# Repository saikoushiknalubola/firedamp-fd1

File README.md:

# Firedamp Dynamics · FD-1 Borehole Sentinel

**Vishwakarma Awards 2026-27** · Sustainable Mining (IIT Hyderabad) · Application ID **VK26-IITH-SM-0008**

**Team Chakra**
- Saikoushik Nalubola (lead), B.Tech CSE (AI & ML), SR University, Warangal
- Devara Aravind, Mining Engineering, University College of Engineering, Osmania University
- Atthe Durga Raj, Mining Engineering, JNTUH University College of Engineering Manthani

India drains methane out of its gassiest coal seams for safety, then mostly lets it go. Ember (2026) found no commercial coal mine methane project running in the country, while emissions are on track to pass 1.6 Mt a year by the end of the decade. Gas can only be used or flared safely when its quality is known, and a single leaking borehole collar can dilute a whole drainage range toward the 5-15% explosive band without anyone seeing which hole is at fault.

Firedamp Dynamics is a five-stage capture system: drainage, conditioning, utilisation, destruction and MRV. **FD-1 is the module we build first.** It sits on each borehole and does four things:

- measures methane (NDIR), oxygen, flow (ISO 5167 orifice) and line pressure at that hole, once a second
- throttles the hole when air leaks in, and isolates it below 25% CH4 or above 10% O2
- checks itself: methane from the NDIR must agree with methane implied by oxygen (1 − O2/20.95)
- logs per-borehole methane totals for MRV, corrected for gas density

## Key numbers

| | |
|---|---|
| Routing bands | route ≥ 30% CH4 (2 × upper explosive limit, UNECE 2016) · throttle 25-30% · isolate < 25% |
| Leak model | moderate leak held at ≥ 28.5% CH4 by throttling; gross leak isolated at 331 s; unmanaged range falls to 17.0% |
| Flow accuracy | density correction removes a 14.4% under-read at 60% CH4 |
| Bracket FEA | rev A FoS 1.87 → rev B FoS 3.87 (12 kg spool at 4 g, Al 6061-T6) |
| Electronics | KiCad 7 schematic (44 parts, 44 nets) and routed 2-layer PCB, 110 × 80 mm, DRC 0 errors |
| Cost | ₹35,400 per complete node · ₹48,400 for the full Stage 3 build incl. bench rig (approximate quotes, Oct 2026) |
| Value | one borehole draining 0.3 m3/min CH4 ≈ $190/day of gas at Ember's import-offset rate |

Every number has a source or a script: see [docs/sources.md](docs/sources.md).

## Repository

| Path | Contents |
|---|---|
| `cad/src/fd1_assembly.py` | Parametric CadQuery model, 24 parts, driven by one parameter block |
| `cad/step/`, `cad/stl/` | STEP for every part plus the assembly; STL for printing (chamber, servo bracket) |
| `electronics/kicad/` | Native KiCad 7 schematic + PCB, netlist, DRC report, Specctra files, generators, renderer |
| `electronics/bom.csv` | Itemised BOM with price basis for every line and the cost decisions behind it |
| `firmware/fd1_node/` | ESP32-S3 firmware: state machine, flow maths, MRV totals, pin map, thresholds |
| `analysis/` | Bracket FEA (scikit-fem), gas and orifice calculations, closed-loop leak model, unit economics |
| `docs/` | Diagram scripts, all deck figures, sources, patent notes |
| `test-rig/test_plan.md` | Eight bench tests with pass criteria |

## Reproduce

```bash
pip install cadquery trimesh scikit-fem matplotlib numpy scipy pygments
python cad/src/fd1_assembly.py && python cad/src/render.py
python analysis/bracket_fea.py && python analysis/gas_calcs.py && python analysis/leak_sim.py
python electronics/bom.py && python electronics/schematic.py
python docs/diagrams.py && python docs/research_figures.py
# KiCad 7 + Freerouting 1.9
cd electronics/kicad && python gen_schematic.py \
  && kicad-cli sch export netlist fd1_controller.kicad_sch -o fd1_controller.net \
  && python check_netlist.py \
  && python gen_pcb.py place \
  && java -jar freerouting-1.9.0.jar -de fd1_controller.dsn -do fd1_controller.ses -mp 60 \
  && python gen_pcb.py finish && python render_pcb.py
```

## Safety

The bench rig runs on CO2 as a non-flammable stand-in for seam gas, with purity read from the O2 cell. The only methane on the bench is a small certified span cylinder at 2.5% (below the lower explosive limit). The prototype is not Ex certified and will not go underground; field equipment needs DGMS approval under the Coal Mines Regulations 2017 and an IEC 60079 Group I design.

## Status

Stage 2 design complete, including a DRC-checked PCB. Next: Gerbers to fab, sensor drivers replacing the firmware stubs, rig build and calibration (roadmap in the deck).

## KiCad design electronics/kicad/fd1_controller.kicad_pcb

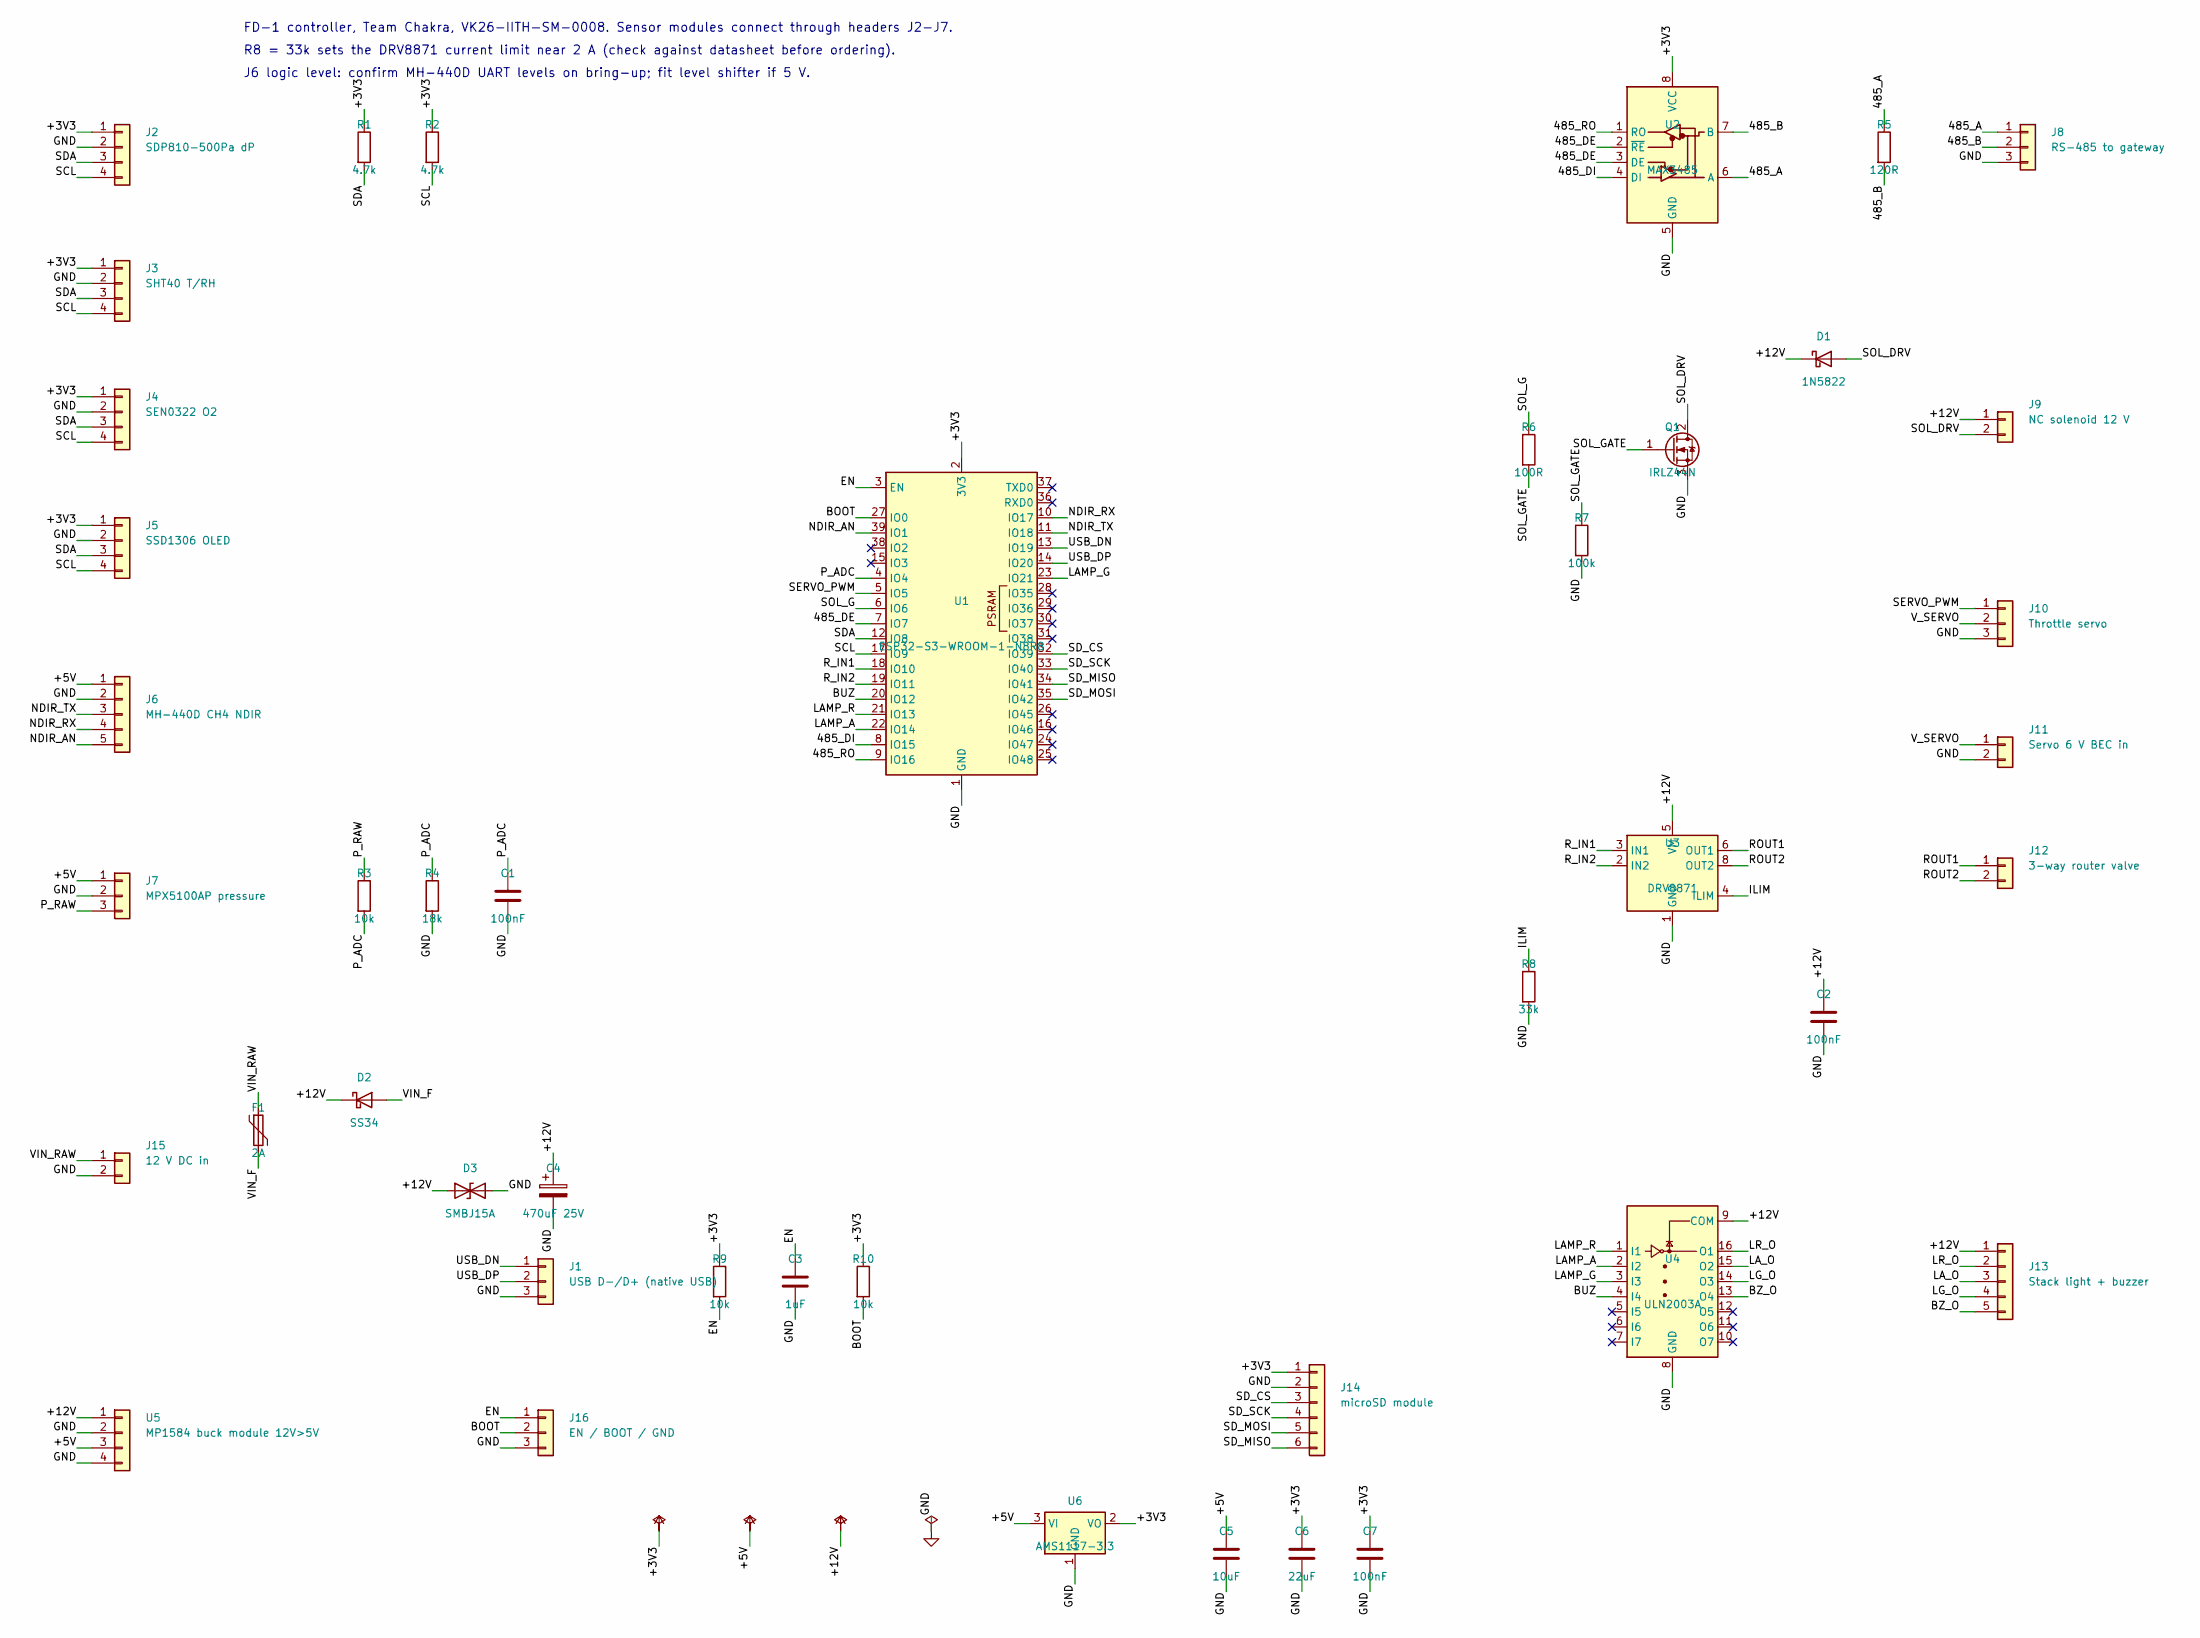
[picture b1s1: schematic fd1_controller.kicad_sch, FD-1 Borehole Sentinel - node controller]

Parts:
C1, C2, C7: 100nF; C_0805_2012Metric
C3: 1uF; C_0805_2012Metric
C4: 470uF 25V; CP_Radial_D10.0mm_P5.00mm
C5: 10uF; C_0805_2012Metric
C6: 22uF; C_0805_2012Metric
D1: 1N5822; D_DO-201AD_P15.24mm_Horizontal
D2: SS34; D_SMA
D3: SMBJ15A; D_SMB
F1: 2A; Fuse_1812_4532Metric
J1: USB D-/D+ (native USB); PinHeader_1x03_P2.54mm_Vertical
J2: SDP810-500Pa dP; PinHeader_1x04_P2.54mm_Vertical
J3: SHT40 T/RH; PinHeader_1x04_P2.54mm_Vertical
J4: SEN0322 O2; PinHeader_1x04_P2.54mm_Vertical
J5: SSD1306 OLED; PinHeader_1x04_P2.54mm_Vertical
J6: MH-440D CH4 NDIR; PinHeader_1x05_P2.54mm_Vertical
J7: MPX5100AP pressure; PinHeader_1x03_P2.54mm_Vertical
J8: RS-485 to gateway; TerminalBlock_bornier-3_P5.08mm
J9: NC solenoid 12 V; TerminalBlock_bornier-2_P5.08mm
J10: Throttle servo; PinHeader_1x03_P2.54mm_Vertical
J11: Servo 6 V BEC in; PinHeader_1x02_P2.54mm_Vertical
J12: 3-way router valve; TerminalBlock_bornier-2_P5.08mm
J13: Stack light + buzzer; PinHeader_1x05_P2.54mm_Vertical
J14: microSD module; PinHeader_1x06_P2.54mm_Vertical
J15: 12 V DC in; TerminalBlock_bornier-2_P5.08mm
J16: EN / BOOT / GND; PinHeader_1x03_P2.54mm_Vertical
Q1: IRLZ44N; TO-220-3_Vertical
R1, R2: 4.7k; R_0805_2012Metric
R3, R9, R10: 10k; R_0805_2012Metric
R4: 18k; R_0805_2012Metric
R5: 120R; R_0805_2012Metric
R6: 100R; R_0805_2012Metric
R7: 100k; R_0805_2012Metric
R8: 33k; R_0805_2012Metric
U1: ESP32-S3-WROOM-1-N8R8; ESP32-S3-WROOM-1
U2: MAX3485; SOIC-8_3.9x4.9mm_P1.27mm
U3: DRV8871; Texas_HTSOP-8-1EP_3.9x4.9mm_P1.27mm_EP2.95x4.9mm_Mask2.4x3.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
U4: ULN2003A; DIP-16_W7.62mm
U5: MP1584 buck module 12V>5V; PinHeader_1x04_P2.54mm_Vertical
U6: AMS1117-3.3; SOT-223-3_TabPin2

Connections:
485_A: J8.1, R5.1, U2.6 (A)
485_B: J8.2, R5.2, U2.7 (B)
485_DE: U1.7 (IO7), U2.2 (~RE), U2.3 (DE)
485_DI: U1.8 (IO15), U2.4 (DI)
485_RO: U1.9 (IO16), U2.1 (RO)
+3V3: C6.1, C7.1, J2.1, J3.1, J4.1, J5.1, J14.1, R1.1, R2.1, R9.1, R10.1, U1.2 (3V3), U2.8 (VCC), U6.2 (VO)
+5V: C5.1, J6.1, J7.1, U5.3, U6.3 (VI)
+12V: C2.1, C4.1, D1.1 (K), D2.1 (K), D3.1 (A1), J9.1, J13.1, U3.5 (VM), U4.9 (COM), U5.1
BOOT: J16.2, R10.2, U1.27 (IO0)
BUZ: U1.20 (IO12), U4.4 (I4)
BZ_O: J13.5, U4.13 (O4)
EN: C3.1, J16.1, R9.2, U1.3 (EN)
GND: C1.2, C2.2, C3.2, C4.2, C5.2, C6.2, C7.2, D3.2 (A2), J1.3, J2.2, J3.2, J4.2, J5.2, J6.2, J7.2, J8.3, J10.3, J11.2, J14.2, J15.2, J16.3, Q1.3 (S), R4.2, R7.2, R8.2, U1.1 (GND), U1.40 (GND), U1.41 (GND), U2.5 (GND), U3.1 (GND), U3.7 (GND), U3.9 (GND), U4.8 (GND), U5.2, U5.4, U6.1 (GND)
ILIM: R8.1, U3.4 (ILIM)
LAMP_A: U1.22 (IO14), U4.2 (I2)
LAMP_G: U1.23 (IO21), U4.3 (I3)
LAMP_R: U1.21 (IO13), U4.1 (I1)
LA_O: J13.3, U4.15 (O2)
LG_O: J13.4, U4.14 (O3)
LR_O: J13.2, U4.16 (O1)
NDIR_AN: J6.5, U1.39 (IO1)
NDIR_RX: J6.4, U1.10 (IO17)
NDIR_TX: J6.3, U1.11 (IO18)
P_ADC: C1.1, R3.2, R4.1, U1.4 (IO4)
P_RAW: J7.3, R3.1
ROUT1: J12.1, U3.6 (OUT1)
ROUT2: J12.2, U3.8 (OUT2)
R_IN1: U1.18 (IO10), U3.3 (IN1)
R_IN2: U1.19 (IO11), U3.2 (IN2)
SCL: J2.4, J3.4, J4.4, J5.4, R2.2, U1.17 (IO9)
SDA: J2.3, J3.3, J4.3, J5.3, R1.2, U1.12 (IO8)
SD_CS: J14.3, U1.32 (IO39)
SD_MISO: J14.6, U1.34 (IO41)
SD_MOSI: J14.5, U1.35 (IO42)
SD_SCK: J14.4, U1.33 (IO40)
SERVO_PWM: J10.1, U1.5 (IO5)
SOL_DRV: D1.2 (A), J9.2, Q1.2 (D)
SOL_G: R6.1, U1.6 (IO6)
SOL_GATE: Q1.1 (G), R6.2, R7.1
USB_DN: J1.1, U1.13 (IO19)
USB_DP: J1.2, U1.14 (IO20)
VIN_F: D2.2 (A), F1.2
VIN_RAW: F1.1, J15.1
V_SERVO: J10.2, J11.1

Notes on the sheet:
FD-1 controller, Team Chakra, VK26-IITH-SM-0008. Sensor modules connect through headers J2-J7.
R8 = 33k sets the DRV8871 current limit near 2 A (check against datasheet before ordering).
J6 logic level: confirm MH-440D UART levels on bring-up; fit level shifter if 5 V.

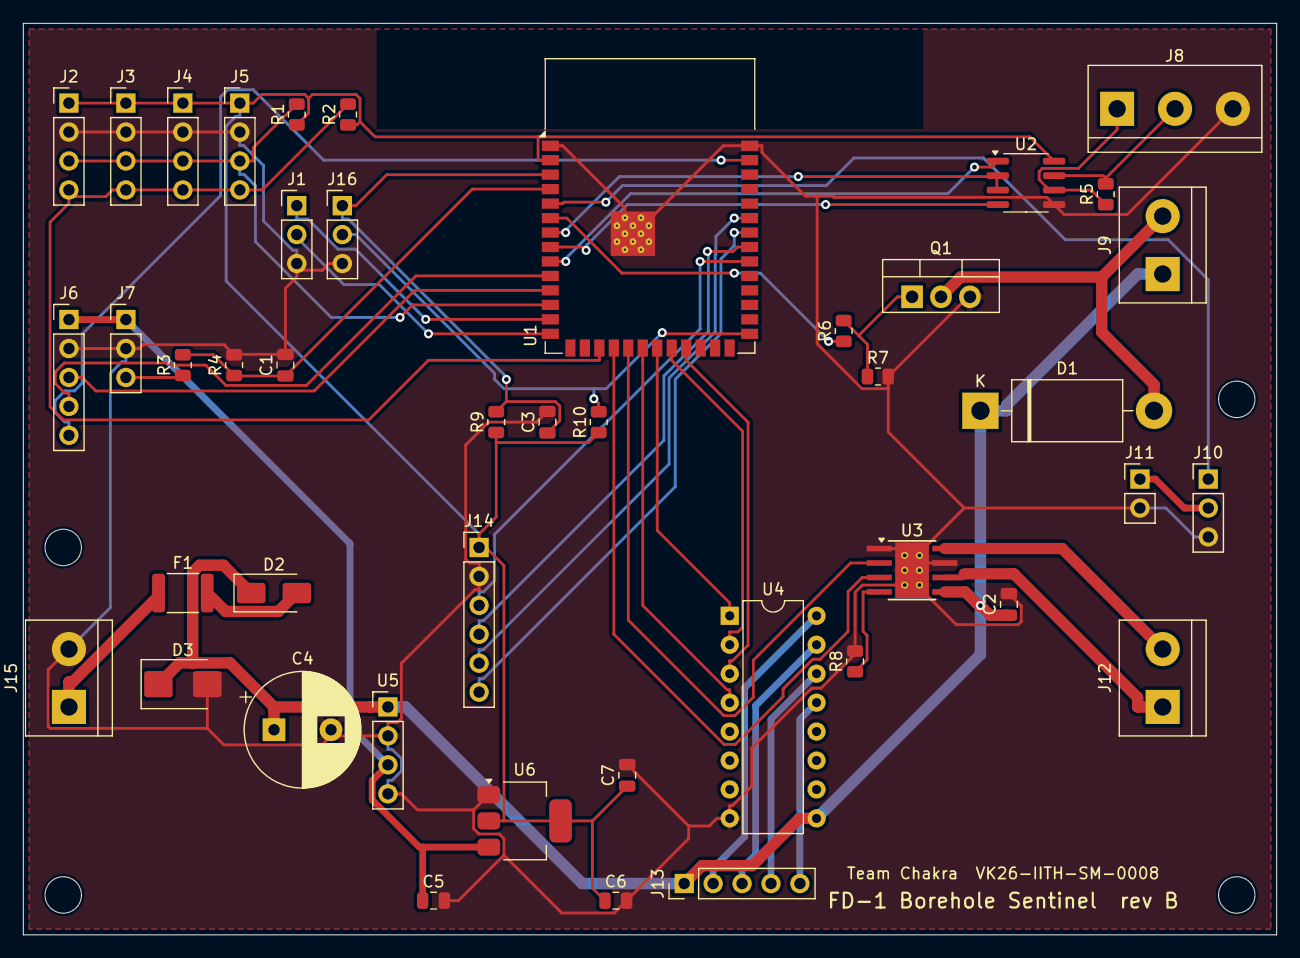
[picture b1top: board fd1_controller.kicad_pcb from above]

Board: 2 copper layers, 110.0 x 80.0 mm, 48 parts (0 on the bottom side), 44 nets.

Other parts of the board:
H1, H2, H3, H4: MountingHole_3.2mm_M3

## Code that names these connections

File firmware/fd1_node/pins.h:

// FD-1 node pin map (ESP32-S3-WROOM-1-N8R8). Mirrors electronics/pinmap.csv.
// GPIO35-37 are reserved for octal PSRAM on N8R8 modules; GPIO19/20 are USB.
#pragma once

#define PIN_I2C_SDA      8
#define PIN_I2C_SCL      9
#define PIN_NDIR_TX     17   // MCU TX -> MH-440D RXD
#define PIN_NDIR_RX     18   // MCU RX <- MH-440D TXD
#define PIN_NDIR_AN      1   // optional: MH-440D analog out (0.4-2.0 V) on ADC1_CH0
#define PIN_P_ADC        4   // MPX5100AP via 10k/18k divider
#define PIN_485_TX      15
#define PIN_485_RX      16
#define PIN_485_DE       7
#define PIN_SOLENOID     6   // IRLZ44N gate, HIGH = valve open (NC valve closes on power loss)
#define PIN_SERVO        5   // throttle servo, LEDC 50 Hz
#define PIN_ROUTER_IN1  10   // DRV8871
#define PIN_ROUTER_IN2  11
#define PIN_LAMP_R      13
#define PIN_LAMP_A      14
#define PIN_LAMP_G      21
#define PIN_BUZZER      12
#define PIN_SD_CS       39
#define PIN_SD_SCK      40
#define PIN_SD_MISO     41
#define PIN_SD_MOSI     42

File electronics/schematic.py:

"""FD-1 node controller: pinout connection diagram + power tree.
Pin map is mirrored in pinmap.csv and firmware/fd1_node/pins.h.
Run: python schematic.py -> ../docs/figures/schematic.png"""
import csv
import os

import matplotlib
matplotlib.use("Agg")
import matplotlib.pyplot as plt
from matplotlib.patches import FancyBboxPatch, Rectangle

HERE = os.path.dirname(os.path.abspath(__file__))
OUT = os.path.join(HERE, "..", "docs", "figures", "schematic.png")
plt.rcParams.update({"font.family": "Inter", "font.size": 7})
INK, NAVY, CYAN, RED, LIME, SLATE = "#0F172A", "#1E3A8A", "#0284C7", "#DC2626", "#65A30D", "#64748B"

# (mcu pin, side, net, device, device pin, colour)
PINS = [
    ("GPIO8", "L", "SDA", "I2C bus", "SDA", CYAN),
    ("GPIO9", "L", "SCL", "I2C bus", "SCL", CYAN),
    ("GPIO17 (U1TX)", "L", "NDIR_RX", "MH-440D", "RXD", NAVY),
    ("GPIO18 (U1RX)", "L", "NDIR_TX", "MH-440D", "TXD", NAVY),
    ("GPIO4 (ADC1_CH3)", "L", "P_ADC", "MPX5100AP", "Vout via 10k/18k", NAVY),
    ("GPIO15 (U2TX)", "R", "485_DI", "MAX3485", "DI", SLATE),
    ("GPIO16 (U2RX)", "R", "485_RO", "MAX3485", "RO", SLATE),
    ("GPIO7", "R", "485_DE", "MAX3485", "DE + /RE", SLATE),
    ("GPIO6", "R", "SOL_G", "IRLZ44N", "Gate via 100R, 100k pull-down", RED),
    ("GPIO5 (LEDC)", "R", "SERVO_PWM", "MG996R", "Signal (50 Hz)", RED),
    ("GPIO10", "R", "R_IN1", "DRV8871", "IN1", RED),
    ("GPIO11", "R", "R_IN2", "DRV8871", "IN2", RED),
    ("GPIO13/14/21", "R", "LAMP_R/A/G", "ULN2003A", "IN1-3 > 12 V stack light", LIME),
    ("GPIO12", "R", "BUZ", "ULN2003A", "IN4 > buzzer", LIME),
    ("GPIO39/40/41/42", "R", "SD_CS/SCK/MISO/MOSI", "microSD", "SPI", LIME),
]


def rbox(ax, x, y, w, h, fc, ec, lw=1.0):
    ax.add_patch(FancyBboxPatch((x, y), w, h, boxstyle="round,pad=0,rounding_size=0.008", fc=fc, ec=ec, lw=lw))


fig = plt.figure(figsize=(12, 6.2), dpi=220)
ax = fig.add_axes([0, 0, 1, 1]); ax.set_xlim(0, 1); ax.set_ylim(0, 1); ax.axis("off")

# MCU
mx, my, mw, mh = 0.40, 0.30, 0.20, 0.62
rbox(ax, mx, my, mw, mh, "#F8FAFC", INK, 1.4)
ax.text(mx + mw / 2, my + mh - 0.03, "U1  ESP32-S3-WROOM-1-N8R8", ha="center", fontsize=8, fontweight="bold")
ax.text(mx + mw / 2, my + mh - 0.06, "3V3 / GND  |  USB-C on GPIO19/20 for flashing", ha="center", fontsize=6.3, color=SLATE)
L = [p for p in PINS if p[1] == "L"]; R = [p for p in PINS if p[1] == "R"]
devL = {"I2C bus": (0.03, 0.70, 0.16, 0.18, "I2C @ 3V3, 4.7k pull-ups\nSDP810-500Pa  0x25\nSHT40  0x44\nSEN0322 O2  0x73\nSSD1306 OLED  0x3C"),
        "MH-440D": (0.03, 0.50, 0.16, 0.12, "MH-440D CH4 NDIR\n5 V supply, UART 9600\n(logic level checked on\nbring-up; shifter footprint)"),
        "MPX5100AP": (0.03, 0.33, 0.16, 0.11, "MPX5100AP abs. pressure\n5 V supply, 0.2-4.7 V out\n10k/18k divider > 3.0 V max")}
ys = {}
for i, p in enumerate(L):
    y = my + mh - 0.12 - i * 0.075
    ax.plot([mx - 0.02, mx], [y, y], color=INK, lw=1)
    ax.text(mx + 0.006, y, p[0], va="center", fontsize=6.5)
    ax.text(mx - 0.025, y + 0.012, p[2], ha="right", fontsize=6.4, color=p[5], fontweight="bold")
    ys[p[0]] = y
for name, (x, y, w, h, t) in devL.items():
    rbox(ax, x, y, w, h, "white", SLATE)
    ax.text(x + 0.008, y + h / 2, t, va="center", fontsize=6.3)
for p in L:
    x, y, w, h, _ = devL[p[3]]
    ax.plot([x + w, mx - 0.02], [y + h / 2, ys[p[0]]], color=p[5], lw=0.9)
    ax.text(x + w + 0.004, y + h / 2 + (0.012 if p[4] in ("SDA", "RXD") else -0.018), p[4], fontsize=5.8, color=p[5])

devR = {"MAX3485": (0.80, 0.80, 0.18, 0.10, "U3 MAX3485, 3V3\nA/B > twisted pair, 120R term.\n> surface gateway (Modbus RTU)"),
        "IRLZ44N": (0.80, 0.665, 0.18, 0.10, "Q1 IRLZ44N low-side switch\nNC solenoid 12 V\n1N5822 flyback across coil"),
        "MG996R": (0.80, 0.585, 0.18, 0.06, "Throttle servo, 5-6 V\n(separate 6 V BEC)"),
        "DRV8871": (0.80, 0.46, 0.18, 0.10, "U4 DRV8871 H-bridge\nVM 12 V > 3-way router valve\nRsense sets 2 A limit"),
        "ULN2003A": (0.80, 0.33, 0.18, 0.10, "U5 ULN2003A sink driver\nR/A/G 12 V stack light\n+ 12 V buzzer"),
        "microSD": (0.80, 0.24, 0.18, 0.06, "microSD, SPI, 3V3\nMRV log buffer")}
for i, p in enumerate(R):
    y = my + mh - 0.12 - i * 0.042
    ax.plot([mx + mw, mx + mw + 0.02], [y, y], color=INK, lw=1)
    ax.text(mx + mw - 0.006, y, p[0], va="center", ha="right", fontsize=6.3)
    ax.text(mx + mw + 0.025, y + 0.008, p[2], fontsize=6.0, color=p[5], fontweight="bold")
    ys[p[0]] = y
for name, (x, y, w, h, t) in devR.items():
    rbox(ax, x, y, w, h, "white", SLATE)
    ax.text(x + 0.008, y + h / 2, t, va="center", fontsize=6.2)
for p in R:
    x, y, w, h, _ = devR[p[3]]
    ax.plot([mx + mw + 0.12, x], [ys[p[0]], y + h / 2], color=p[5], lw=0.8)
    ax.plot([mx + mw + 0.02, mx + mw + 0.12], [ys[p[0]], ys[p[0]]], color=p[5], lw=0.8)

# power tree
rbox(ax, 0.03, 0.03, 0.94, 0.17, "#F8FAFC", INK)
ax.text(0.04, 0.175, "POWER DISTRIBUTION", fontsize=7.5, fontweight="bold")
chain = [("J1  12 V DC in\n(bench PSU 3 A)", "#fff"), ("D1 SS34 reverse\n+ F1 2 A polyfuse", "#fff"),
         ("D2 SMBJ15A TVS\nC1 470 uF / 25 V", "#fff"), ("U6 MP1584\n12 V > 5.0 V, 3 A", "#fff"),
         ("U7 AMS1117-3.3\n5 V > 3.3 V, 1 A", "#fff")]
for i, (t, fc) in enumerate(chain):
    x = 0.05 + i * 0.152
    rbox(ax, x, 0.06, 0.118, 0.09, fc, NAVY)
    ax.text(x + 0.059, 0.105, t, ha="center", va="center", fontsize=6.3)
    if i:
        ax.annotate("", xy=(x, 0.105), xytext=(x - 0.035, 0.105), arrowprops=dict(arrowstyle="-|>", color=NAVY, lw=1))
ax.text(0.80, 0.14, "+12 V rail: solenoid, DRV8871,\nULN2003A loads", fontsize=6.0, color=RED)
ax.text(0.80, 0.095, "+5 V rail: MH-440D, MPX5100AP", fontsize=6.0, color=NAVY)
ax.text(0.80, 0.06, "+3V3: MCU, I2C, MAX3485, SD", fontsize=6.0, color=CYAN)
fig.savefig(OUT, facecolor="white")

with open(os.path.join(HERE, "pinmap.csv"), "w", newline="") as f:
    w = csv.writer(f); w.writerow(["mcu_pin", "net", "device", "device_pin"])
    for p in PINS:
        w.writerow([p[0], p[2], p[3], p[4]])
print("saved")
